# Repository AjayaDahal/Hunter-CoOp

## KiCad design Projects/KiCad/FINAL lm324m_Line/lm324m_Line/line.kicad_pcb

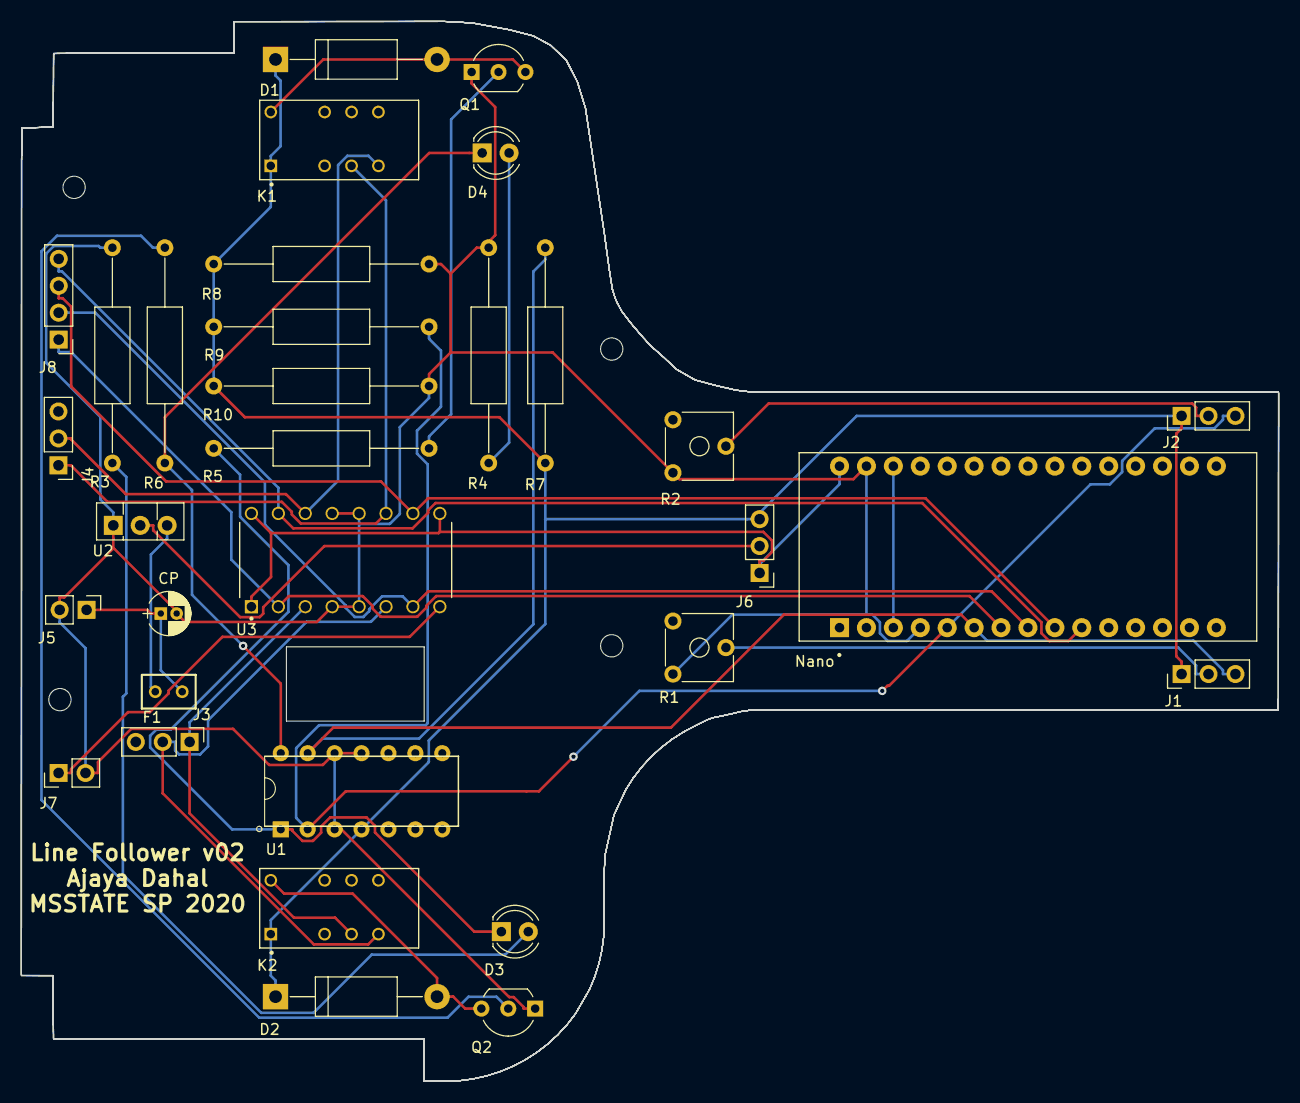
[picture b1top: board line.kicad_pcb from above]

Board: 2 copper layers, 118.6 x 100.0 mm, 36 parts (0 on the bottom side), 28 nets.

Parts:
CP: 0.1uf1; CP_Radial_D4.0mm_P1.50mm
D1, D2: 1N4001; D_DO-15_P15.24mm_Horizontal
D3, D4: LED; LED_D4.0mm
F1: FUSE; C320C
J1, J2: CONN_01X03_MALE (DATA) PIN 3; PinHeader_1x03_P2.54mm_Vertical
J3, J4: CONN_01X03_MALE; PinHeader_1x03_P2.54mm_Vertical
J5: Screw_Terminal_1x02; PinHeader_1x02_P2.54mm_Vertical
J6: CONN_01X03_MALE 1-Ard; PinHeader_1x03_P2.54mm_Vertical
J7: 9V+; PinHeader_1x02_P2.54mm_Vertical
J8: CONN Arduino Backup Motor driver; PinHeader_1x04_P2.54mm_Vertical
K1, K2: EC2-5NU; RELAY_EC2-5NU
Nano: ARDUINO_NANO; SHIELD_ARDUINO_NANO
Q1, Q2: 2N3904; TO-92_Inline_Wide
R1, R2: 10k; Potentiometer_Trimmer_ACP_CA6v_Horizontal
R3, R4: 270; R_Axial_DIN0309_L9.0mm_D3.2mm_P20.32mm_Horizontal
R5, R6: 1k; R_Axial_DIN0309_L9.0mm_D3.2mm_P20.32mm_Horizontal
R7, R9: 10k; R_Axial_DIN0309_L9.0mm_D3.2mm_P20.32mm_Horizontal
R8, R10: 470R; R_Axial_DIN0309_L9.0mm_D3.2mm_P20.32mm_Horizontal
U1: lm324; LM324N
U2: AMS1117-5.0; TO-126_Vertical
U3: L293D; DIP880W50P254L2000H510Q16
hole1: 1; MountingHole_2.1mm
hole2: 2; MountingHole_2.1mm
hole3, hole4: 4; MountingHole_2.1mm

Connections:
5V+ard: J6.1, Nano.30, U3.1, U3.9, U3.16
9V+: J7.1, U3.8
+9V: CP.1, F1.1, J5.1
GND: CP.2, J5.2, J7.2, Nano.4, Nano.29, Q1.1, Q2.1, R1.1, R2.1, R3.2, R4.2, R8.2, R10.2, U1.3, U1.11, U1.12, U2.1, U3.4, U3.5, U3.12, U3.13
Input1-: J2.3, Nano.5, R9.2, U1.2
Input4-: J1.3, Nano.6, R7.2, U1.13
Motor1a: J3.1, K2.4, U3.3
Motor1b: J3.2, K2.5, U3.6
Motor2a: J4.1, K1.4, U3.11
Motor2b: J4.2, K1.5, U3.14
unnamed: D1.2, K1.12, Q1.3
unnamed: D2.2, K2.12, Q2.3
unnamed: D3.2, R3.1
unnamed: D4.2, R4.1
unnamed: F1.2, U2.3
unnamed: J1.2, R1.2
unnamed: J2.2, R2.2
unnamed: J6.2, U2.2
unnamed: Q1.2, R5.2
unnamed: Q2.2, R6.2
unnamed: Nano.3, Nano.28
OutputPIN1: D3.1, R5.1, U1.1
OutputPIN4: D4.1, R6.1, U1.14
V+: D1.1, D2.1, J1.1, J2.1, J6.3, K1.1, K2.1, R7.1, R8.1, R9.1, R10.1, U1.4
arOutputPIN1: J8.1, Nano.7, U3.2
arOutputPIN2: J8.2, Nano.8, U3.7
arOutputPIN3: J8.3, Nano.9, U3.10
arOutputPIN4: J8.4, Nano.10, U3.15
